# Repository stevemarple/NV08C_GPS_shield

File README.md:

# NV08C_GPS_shield

Arduino shield supporting the NV08C-CSM GNSS (GPS/GLONASS/Galileo)
receiver module.

## License

Unless indicated otherwise hardware is released under the Creative
Commons Attribution-ShareAlike 3.0 Unported (CC BY-SA 3.0)
http://creativecommons.org/licenses/by-sa/3.0/

Unless indicated otherwise software is released under the GNU Lesser
General Public License, version 2.1.
http://www.gnu.org/licenses/lgpl-2.1.html

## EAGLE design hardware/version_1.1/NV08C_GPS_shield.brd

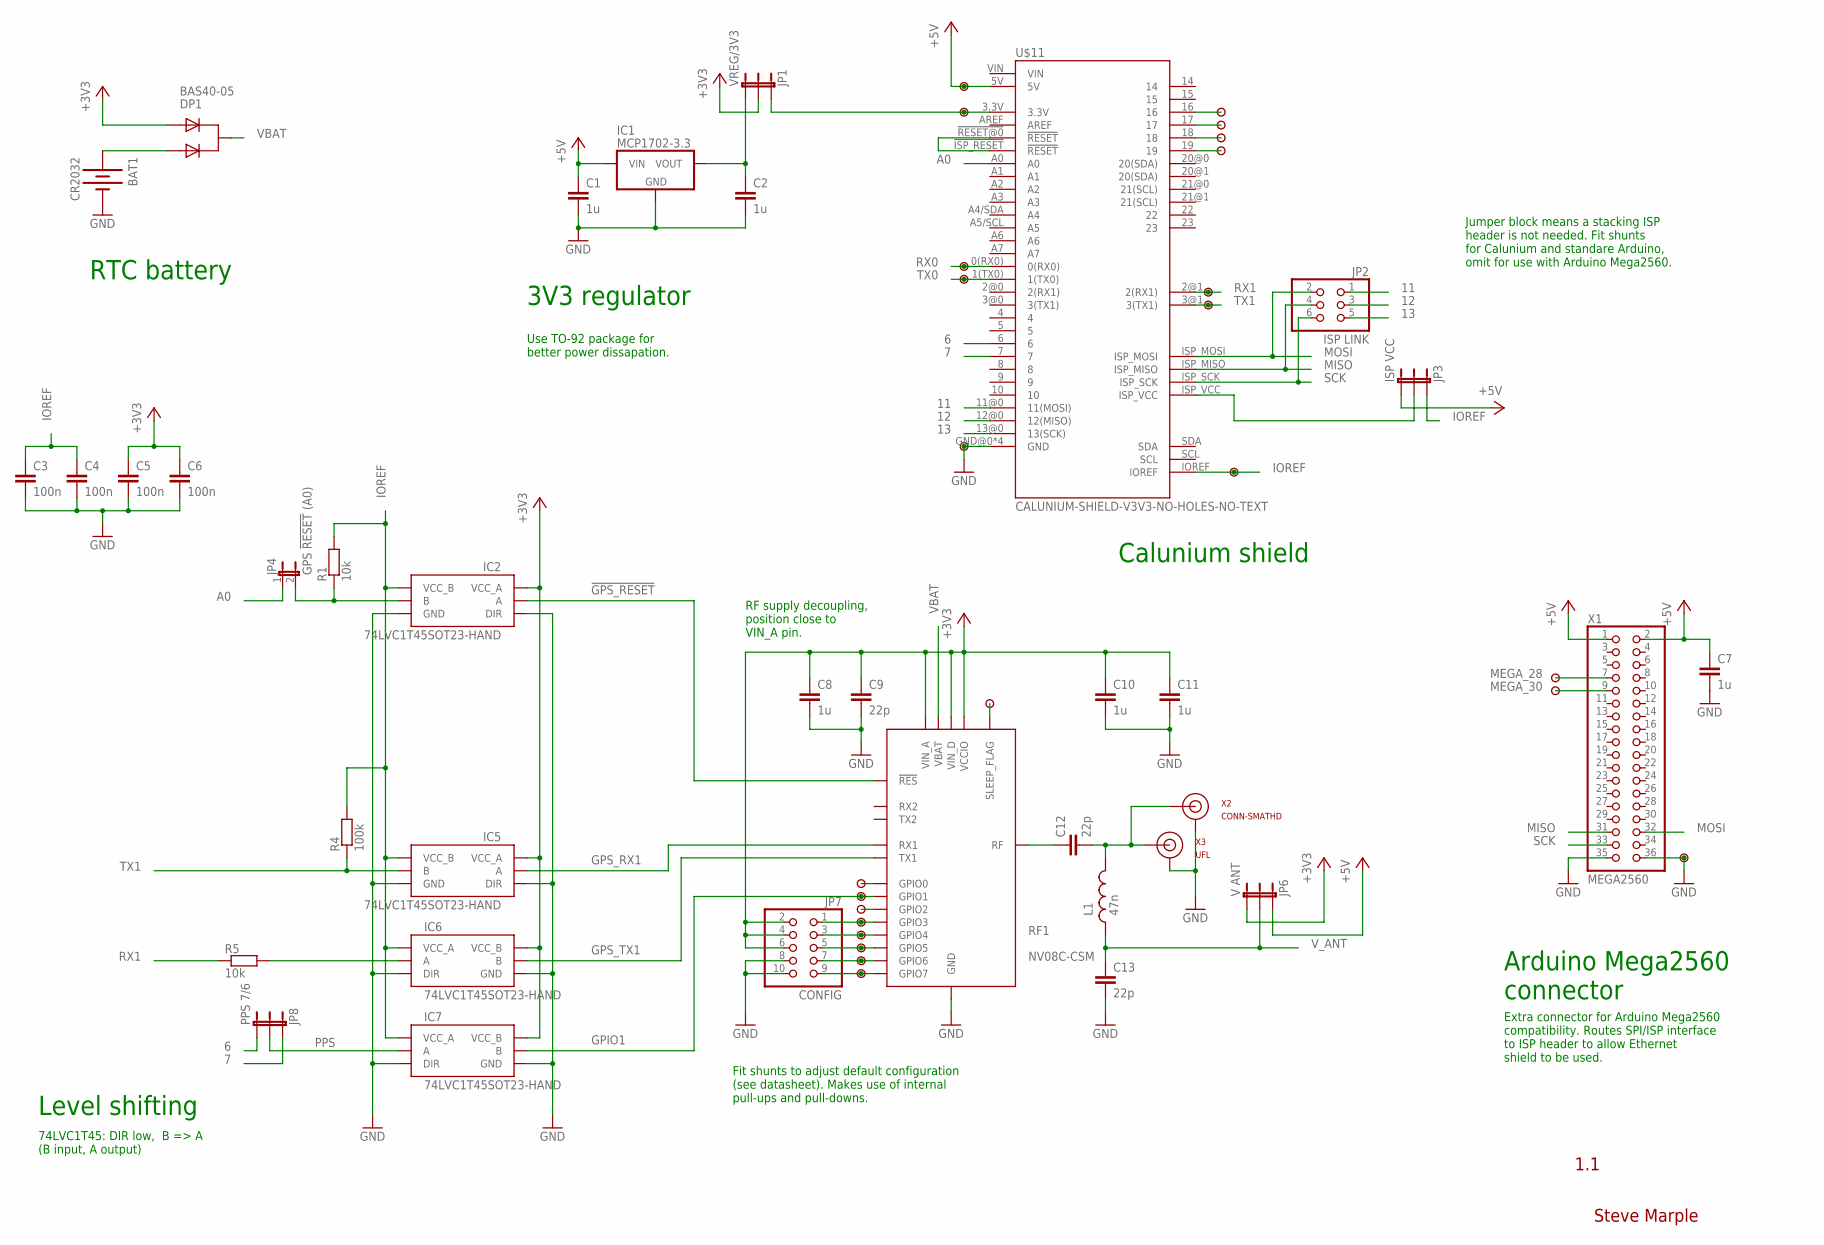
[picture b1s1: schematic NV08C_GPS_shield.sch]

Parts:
BAT1: CR2032; BATTCOM_20MM_PTH
C1, C2, C7, C8, C10, C11: 1u; 1206-HAND
C3, C4, C5, C6: 100n; 1206-HAND
C9, C12, C13: 22p; 0805-HAND
DP1: BAS40-05; SOT23-3-HAND
IC1: MCP1702-3.3; TO-92
IC2, IC5, IC6, IC7: 74LVC1T45SOT23-HAND; SOT23-6-HAND
JP1: VREG/3V3; 1X03
JP2: ISP LINK; 2X03
JP3: ISP VCC; 1X03
JP4: GPS !RESET! (A0); 1X02
JP6: V ANT; 1X03
JP7: CONFIG; 2X05
JP8: PPS 7/6; 1X03
L1: 47n; 0805-HAND
R1, R5: 10k; 1206-HAND
R4: 100k; 1206-HAND
RF1: NV08C-CSM; NVC08C-CSM-HAND
U$1, U$2, U$3, U$4, U$5, U$6, U$7, U$8, U$9, U$10, U$12, U$13, U$14, U$15, U$16, U$17, U$18, U$19, U$21, U$22, U$23, U$24, U$25: PAD
U$11: CALUNIUM-SHIELD-V3V3-NO-HOLES-NO-TEXT; CALUNIUM-SHIELD-NO-OUTLINE-NO-HOLES-NO-TEXT-V3
U$20: ?; PAD
X1: MEGA2560; 2X18
X2: CONN-SMATHD; SMA-THD
X3: UFL; CONN-UFL-HAND-SOLDERING

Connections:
3V3_SHIELD: JP1.1, U$2.1, U$11.3.3V
6: JP8.3, U$11.6
7: JP8.1, U$11.7
11: JP2.1, U$11.11@0 (11(MOSI))
12: JP2.3, U$11.12@0 (12(MISO))
13: JP2.5, U$11.13@0 (13(SCK))
!GPS_RESET: IC2.3 (A), RF1.P$25 (!RES)
!RESET: U$11.!ISP_RESET (!RESET), U$11.!RESET@0 (!RESET)
+3V3: C5.1, C6.1, C8.1, C9.1, C10.1, C11.1, DP1.2 (A2), IC2.1 (VCC_A), IC5.1 (VCC_A), IC6.6 (VCC_B), IC7.6 (VCC_B), JP1.2, JP6.3, JP7.2, JP7.4, JP7.6, RF1.P$8 (VIN_A), RF1.P$26 (VIN_D), RF1.P$28 (VCCIO)
+5V: C1.1, C7.1, IC1.2 (VIN), JP3.3, JP6.1, U$1.1, U$11.5V, X1.1, X1.2
A0: JP4.1, U$11.A0
GND: BAT1.2 (-), C1.2, C2.2, C3.2, C4.2, C5.2, C6.2, C7.2, C8.2, C9.2, C10.2, C11.2, C13.2, IC1.1 (GND), IC2.2 (GND), IC2.5 (DIR), IC5.2 (GND), IC5.5 (DIR), IC6.2 (GND), IC6.5 (DIR), IC7.2 (GND), IC7.5 (DIR), JP7.8, JP7.10, RF1.P$3 (GND), RF1.P$9 (GND), RF1.P$10 (GND), RF1.P$11 (GND), RF1.P$12 (GND), RF1.P$13 (GND), RF1.P$14 (GND), RF1.P$16 (GND), RF1.P$17 (GND), RF1.P$18 (GND), RF1.P$19 (GND), RF1.P$22 (GND), RF1.P$24 (GND), RF1.P$27 (GND), RF1.P$29 (GND), RF1.P$34 (GND), U$11.GND@0 (GND), U$11.GND@1 (GND), U$11.GND@2 (GND), U$11.GND@3 (GND), U$12.1, U$17.1, X1.35, X1.36, X2.GND@0 (GND), X2.GND@1 (GND), X2.GND@2 (GND), X2.GND@3 (GND), X3.GND@0 (GND), X3.GND@1 (GND)
GPIO0: RF1.P$20 (GPIO0), U$18.1
GPIO1: IC7.4 (B), RF1.P$2 (GPIO1), U$19.1
GPIO2: RF1.P$1 (GPIO2), U$20.1
GPIO3: JP7.1, RF1.P$6 (GPIO3), U$21.1
GPIO4: JP7.3, RF1.P$7 (GPIO4), U$22.1
GPIO5: JP7.5, RF1.P$4 (GPIO5), U$23.1
GPIO6: JP7.7, RF1.P$35 (GPIO6), U$24.1
GPIO7: JP7.9, RF1.P$5 (GPIO7), U$25.1
GPS_RX1: IC5.3 (A), RF1.P$33 (RX1)
GPS_TX1: IC6.4 (B), RF1.P$32 (TX1)
IOREF: C3.1, C4.1, IC2.6 (VCC_B), IC5.6 (VCC_B), IC6.1 (VCC_A), IC7.1 (VCC_A), JP3.1, R1.2, R4.2, U$11.IOREF, U$13.1
ISP_VCC: JP3.2, U$11.ISP_VCC
MEGA_28: U$14.1, X1.7
MEGA_30: U$15.1, X1.9
MISO: JP2.4, U$11.ISP_MISO, X1.31
MOSI: JP2.2, U$11.ISP_MOSI, X1.32
unnamed: C2.1, IC1.3 (VOUT), JP1.3
unnamed: U$6.1, U$11.19
unnamed: C12.2, L1.2, X2.SIG (SIGNAL), X3.SIGNAL
unnamed: IC6.3 (A), R5.2
unnamed: U$5.1, U$11.18
unnamed: C12.1, RF1.P$15 (RF)
unnamed: IC2.4 (B), JP4.2, R1.1
unnamed: U$4.1, U$11.17
unnamed: U$3.1, U$11.16
PPS: IC7.3 (A), JP8.2
RX0: U$7.1, U$11.0(RX0)
RX1: R5.1, U$9.1, U$11.2@1 (2(RX1))
SCK: JP2.6, U$11.ISP_SCK, X1.33
SLEEP_FLAG: RF1.P$21 (SLEEP_FLAG), U$16.1
TX0: U$8.1, U$11.1(TX0)
TX1: IC5.4 (B), R4.1, U$10.1, U$11.3@1 (3(TX1))
VBAT: DP1.3 (C), RF1.P$23 (VBAT)
VBATT: BAT1.1 (+), DP1.1 (A1)
V_ANT: C13.1, JP6.2, L1.1

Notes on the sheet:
1.1
Steve Marple
Level shifting
3V3 regulator
RTC battery
74LVC1T45: DIR low, B => A (B input, A output)
RF supply decoupling, position close to VIN_A pin.
Use TO-92 package for better power dissapation.
Calunium shield
Arduino Mega2560 connector
Extra connector for Arduino Mega2560 compatibility. Routes SPI/ISP interface to ISP header to allow Ethernet shield to be used.
Jumper block means a stacking ISP header is not needed. Fit shunts for Calunium and standare Arduino, omit for use with Arduino Mega2560.
Fit shunts to adjust default configuration (see datasheet). Makes use of internal pull-ups and pull-downs.

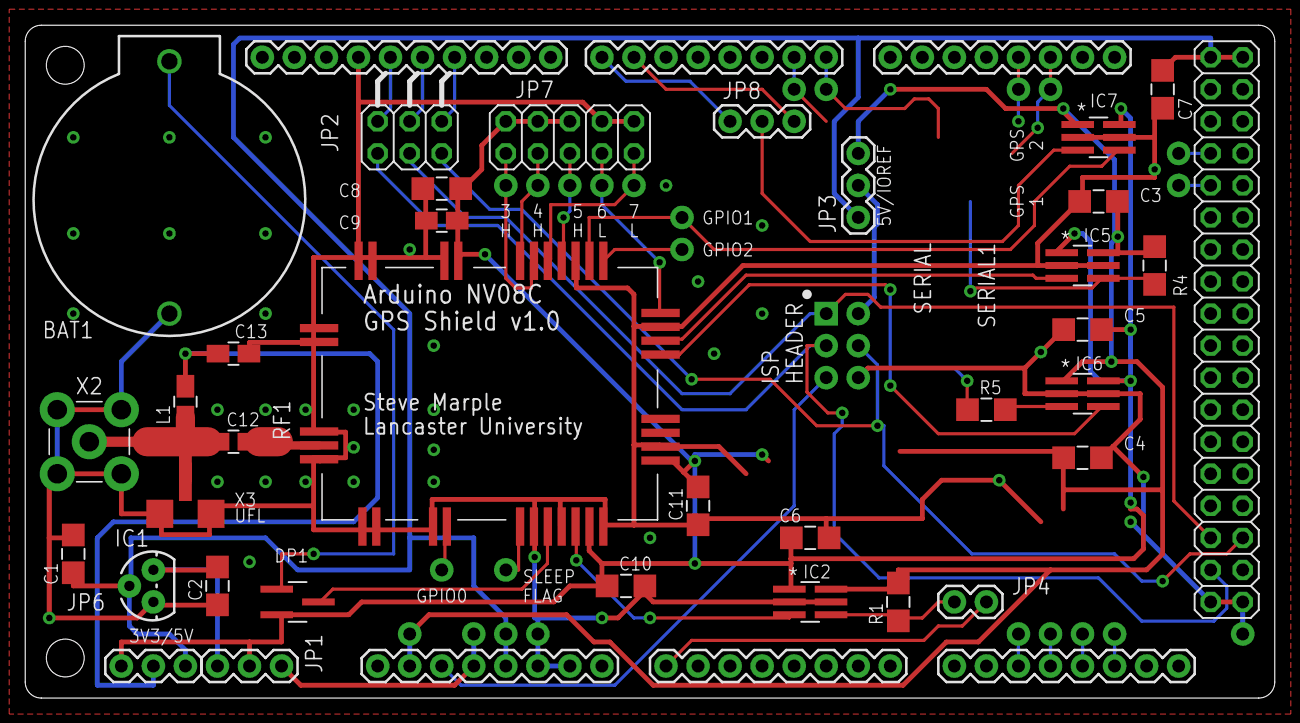
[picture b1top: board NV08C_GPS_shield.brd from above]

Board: 2 copper layers, 99.1 x 53.3 mm, 60 parts (0 on the bottom side), 47 nets.

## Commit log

2014-05-08 Adding design files.
2014-05-08 Adding SteveMarple-Eagle library.
2014-05-08 Changed BAS32L to BAV70.
2014-05-18 Switching to 0805 packages for some parts.
2014-05-18 Layout changes and some missing pin connections made.
2014-05-18 Adding protection resistors in GPS TX lines.
    Enables the same UART to be used to access the bootloader during the boot
    sequence without damaging the level shifters or external FTDI device.
2014-05-19 Change PPS pin used. Add decoupling for NV08C module.
2014-05-20 Minor layout and silkscreen fixes.
2014-05-20 Layout and silkscreen changes. Ground pour added.
2014-05-21 Minor routing and silkscreen changes. Extra pads added.
    Adding extra pads to access unused Arduino pins for easier hacking.
2014-05-21 Minor layout changes.
2014-05-21 Adjusting position of NV08C GPS module and some other components.
    NV08C moved 0.1" left.
2014-05-21 Minor changes to improve SCK routing and GND fill.
2014-05-21 Fixing existing comments and adding new ones.
2014-05-21 Adding CAM file for Iteadstudio PCB service.
    Modified version which outputs _tsilk and _bsilk layers.
2014-05-21 Adding Gerber files.
2014-05-21 Ignoring Eagle backup files.
2014-05-21 Updating to latest version of library.
2014-05-24 Fixing text objects in drawing frame.
2014-05-24 Translate to (0,0). Minor silkscreen changes.
2014-05-24 Revised Gerber files.
2014-05-24 Adding PDFs of schematic and PCB.
2014-06-12 Putting hardware files in spearate directory.
2014-06-12 Creating separate hardware directory.
2014-06-12 Removing old Steve-Marple-Eagle-Library.
2014-06-12 Adding Steve-Marple-Eagle-Library into new hardware directory.
2014-06-12 Moving PDF files to hardware directory.
2014-06-18 Adding sketch to output IRIG-B type timting data for IRIS.
2014-06-18 Adding dependency information.
2014-06-18 Adding README.md describing the project and licensing information.
2014-06-18 Adding 8 second watchdog timer.
2014-06-18 Fix off-by-one error, 'Z' = 35 satellites.
2014-06-20 Adding basic build instructions and hardware configuration details.
2014-07-15 Fixing units, tens, hundreds order for time and day of year.
2014-07-15 Adding firmware files.
2014-11-08 Update README.md
    Correct jumper block name.
2015-08-31 Adding descriptions of all jumper configurations.
2015-08-31 Fixing descriptions for jumpers.
2017-02-14 Add hardware version 1.1
